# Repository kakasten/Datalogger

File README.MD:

# 🎲 Distributed Data Acquisition Platform for Race Vehicles

> A modular, scalable, engineering-driven architecture for high-performance vehicle instrumentation.

---

## 📖 Overview

This project is the development of a **distributed data acquisition platform** for race vehicles, designed to provide a modular, scalable, and easy-to-maintain architecture — capable of evolving continuously alongside the team's needs.

Built for **Formula SAE** vehicles, the system acquires data from analog, digital, frequency, and CAN sensors, transmits the information over a **CAN** network, and centralizes logging, processing, and telemetry in the Master module.

Unlike traditional systems, which centralize all instrumentation in a single acquisition unit, this platform adopts an architecture composed of one **Master module** and **multiple Slave modules**, distributed throughout the vehicle and placed close to the sensors they monitor.

**Key features:**

- ✅ Distributed acquisition
- ✅ CAN Bus communication
- ✅ Modular hardware
- ✅ Local data logging
- ✅ Telemetry support
- ✅ Fault isolation
- ✅ Expandable architecture

> More than a conventional datalogger, this is an open hardware, firmware, and documentation ecosystem, built to grow alongside the team.

---

## 🎯 The Problem We Solve

Centralized acquisition systems have well-known limitations in race vehicles:

- **Long, complex wiring harnesses**, with dozens of meters of cable running across the vehicle to a single central unit
- **High susceptibility to electromagnetic noise**, since low-amplitude analog signals must travel long distances before being conditioned
- **Difficult maintenance and expansion**, since every new sensor requires running a new cable to the central unit
- **Low scalability**, since expansion capacity is limited by the number of physical inputs on the central unit

Our approach solves these problems by **bringing processing to the sensor**, rather than the other way around.

---

## 🧩 System Architecture

### Selected Processing Units

The current hardware definition uses the following processing units:

| System role | Component | Responsibility |
| --- | --- | --- |
| Master | **Milk-V DUO S** (MPU) | High-level processing, data logging, telemetry, and system management |
| Slave | **STM32G431C8T6TR** (MCU) | Local sensor acquisition, signal processing, and CAN communication |

The platform is organized into two core functional blocks:

### 🔹 Master Module

The Master module is the platform's **central management point**. Its responsibilities include:

- Coordinating communication between the modules distributed across the vehicle
- Synchronizing data acquisition across all Slave modules
- Storing the data logged during vehicle operation
- Making data available to external analysis and development tools

The Master's architecture is designed to be **independent of specific implementation technologies** — allowing different software solutions, operating systems, communication protocols, or storage formats to be adopted as the project evolves, without compromising the platform's overall organization.

In the current implementation, the Master runs on the **Milk-V DUO S**, the selected **MPU (Microprocessor Unit)**, using an **RTOS (Real-Time Operating System)** as its software framework, responsible for coordinating logging, processing, and telemetry tasks.

### 🔹 Slave Modules

Slave modules are responsible for **local acquisition** of signals coming from the sensors. Close to the signal source, each module performs:

- Signal conditioning and filtering
- Analog-to-digital conversion
- Initial data processing
- Delivery of processed data to the vehicle's communication network

Each Slave is built around the **STM32G431C8T6TR**, the selected **MCU (Microcontroller Unit)**, responsible for local acquisition and for communicating over the **CAN** bus, which connects all modules to the Master.

Each module can be **specialized** according to the type of signal it needs to acquire:

| Module Type | Application |
| --- | --- |
| High-precision analog inputs | Pressure, temperature, potentiometer sensors |
| Digital inputs | On/off signals, buttons, limit switches |
| Timer capture | Wheel speed, RPM |
| Inertial sensors (IMU) | Acceleration, gyroscope |
| Suspension position | Vertical travel, suspension stroke |
| Custom modules | Application-specific sensors |

This specialization allows **hardware to be optimized for each module's function**, reducing cost, simplifying the electronic design, and increasing overall system reliability.

### 🔄 Communication Topology (High-Level View)

```text
                              ┌────────────────────────────┐
                              │           Master           │
                              │            MPU             │
                              │     RTOS • Data Logging    │
                              └────────────┬───────────────┘
                                           │
                                       CAN Network
                                           │
                 ┌─────────────────────────┴───────────────────────┐
                 │                                                 │
      ┌──────────▼──────────┐                           ┌──────────▼──────────┐
      │       Slave A       │                           │       Slave B       │
      │         MCU         │                           │         MCU         │
      │ Analog • Digital IO │                           │ Analog • Digital IO │
      └──────────┬──────────┘                           └──────────┬──────────┘
                 │                                                 │
          Vehicle Sensors                                   Vehicle Sensors
```

### 📊 Data Flow

1. Sensors generate raw electrical signals
2. Slave modules acquire and condition these signals locally
3. Measurements are transmitted over the **CAN** bus
4. The Master receives all messages from the network
5. Data is logged and, optionally, transmitted via real-time telemetry

### 🔗 Communication Architecture

Each communication interface is chosen based on bandwidth, latency, reliability, and hardware requirements:

- **CAN Bus** — the system's backbone, connecting the Master to one or more Slave modules
- **I²C / SPI / UART** — local interfaces between each module (Master or Slave) and its directly connected peripherals/sensors

```text
                              ┌─────────────────────────┐
                              │         Master          │
                              │           MPU           │
                              └────────────┬────────────┘
                                           │
                                      CAN Network
                                           │
                 ┌─────────────────────────┴───────────────────────┐
                 │                                                 │
      ┌──────────▼──────────┐                           ┌──────────▼──────────┐
      │       Slave A       │                           │       Slave B       │
      │         MCU         │                           │         MCU         │
      └──────────┬──────────┘                           └──────────┬──────────┘
                 │                                                 │
          I²C • SPI • UART                                  I²C • SPI • UART
                 │                                                 │
          Vehicle Sensors                                   Vehicle Sensors
```

---

## 🔌 Wiring Example

One of the main gains of the distributed architecture is the **drastic reduction in wiring harness complexity**. Instead of long individual cables running from each sensor to a central unit, each Slave module sits close to its own set of sensors, and only a shared communication bus runs across the vehicle.

**Conceptual comparison:**

| Aspect | Centralized System | Distributed System (this project) |
| --- | --- | --- |
| Total cable length | High | Reduced |
| Noise susceptibility | High (long analog signal runs) | Low (signal digitized close to source) |
| Ease of maintenance | Low | High |
| Scalability | Limited | High (just add a new module to the bus) |

---

## ⚙️ Engineering Philosophy

Since its inception, the project has prioritized a **clear separation between hardware, firmware, and development infrastructure**. Each component is developed as an independent module with well-defined interfaces, which ensures:

- ♻️ **Code reuse** across different modules and projects
- 🔧 **Simplified maintenance**, since each part can be modified independently
- 📈 **Easier future expansion**, without needing to restructure the entire platform
- 🔀 **Coexistence of hardware versions**, allowing gradual evolution without breaking compatibility

### 📚 Documented Engineering

More than a source code repository, this project is meant to be a **complete record of the engineering behind its development**. From the earliest stages, we aim to document:

- Architecture decisions and their technical rationale
- Functional diagrams and schematics
- Communication flows between modules
- Hardware version history
- Validation procedures and experimental results

This approach turns the repository into a **technical knowledge base**, valuable both for current developers and for future generations of the team.

---

## 🚀 Why Support This Project

This project goes beyond a one-off telemetry system — it represents an **investment in reusable engineering infrastructure**:

- **Common foundation for multiple applications**: rather than a one-off solution, the platform serves as a foundation for different instrumentation systems, from low-frequency measurements to high-speed signals requiring precise timing
- **Technical development for the team**: development spans embedded hardware, firmware, communication protocols, software engineering, and technical documentation — high-value skills for team members
- **Visibility and branding**: the project's public, well-structured documentation serves as a technical showcase for sponsors and partners
- **Continuity**: the emphasis on documentation and modularity ensures that today's investment keeps generating value across future generations of the system

Companies and sponsors interested in supporting the project can get in touch through the channels listed in the [Contact](#-contact) section.

---

## 🤝 Contributing

Contributions are welcome! To propose improvements, fixes, or new features:

1. Fork this repository
2. Create a branch for your change (`git checkout -b feature/feature-name`)
3. Commit your changes (`git commit -m 'Add new feature'`)
4. Push to the remote repository (`git push origin feature/feature-name`)
5. Open a Pull Request

---

## 📬 Contact

For questions, partnerships, or sponsorship proposals, get in touch with the team:

- **Email:** _luizfernandosilveriofelisbino@gmail.com_

---

## 📄 License

This project is distributed under the **[Apache License 2.0](LICENSE)**.

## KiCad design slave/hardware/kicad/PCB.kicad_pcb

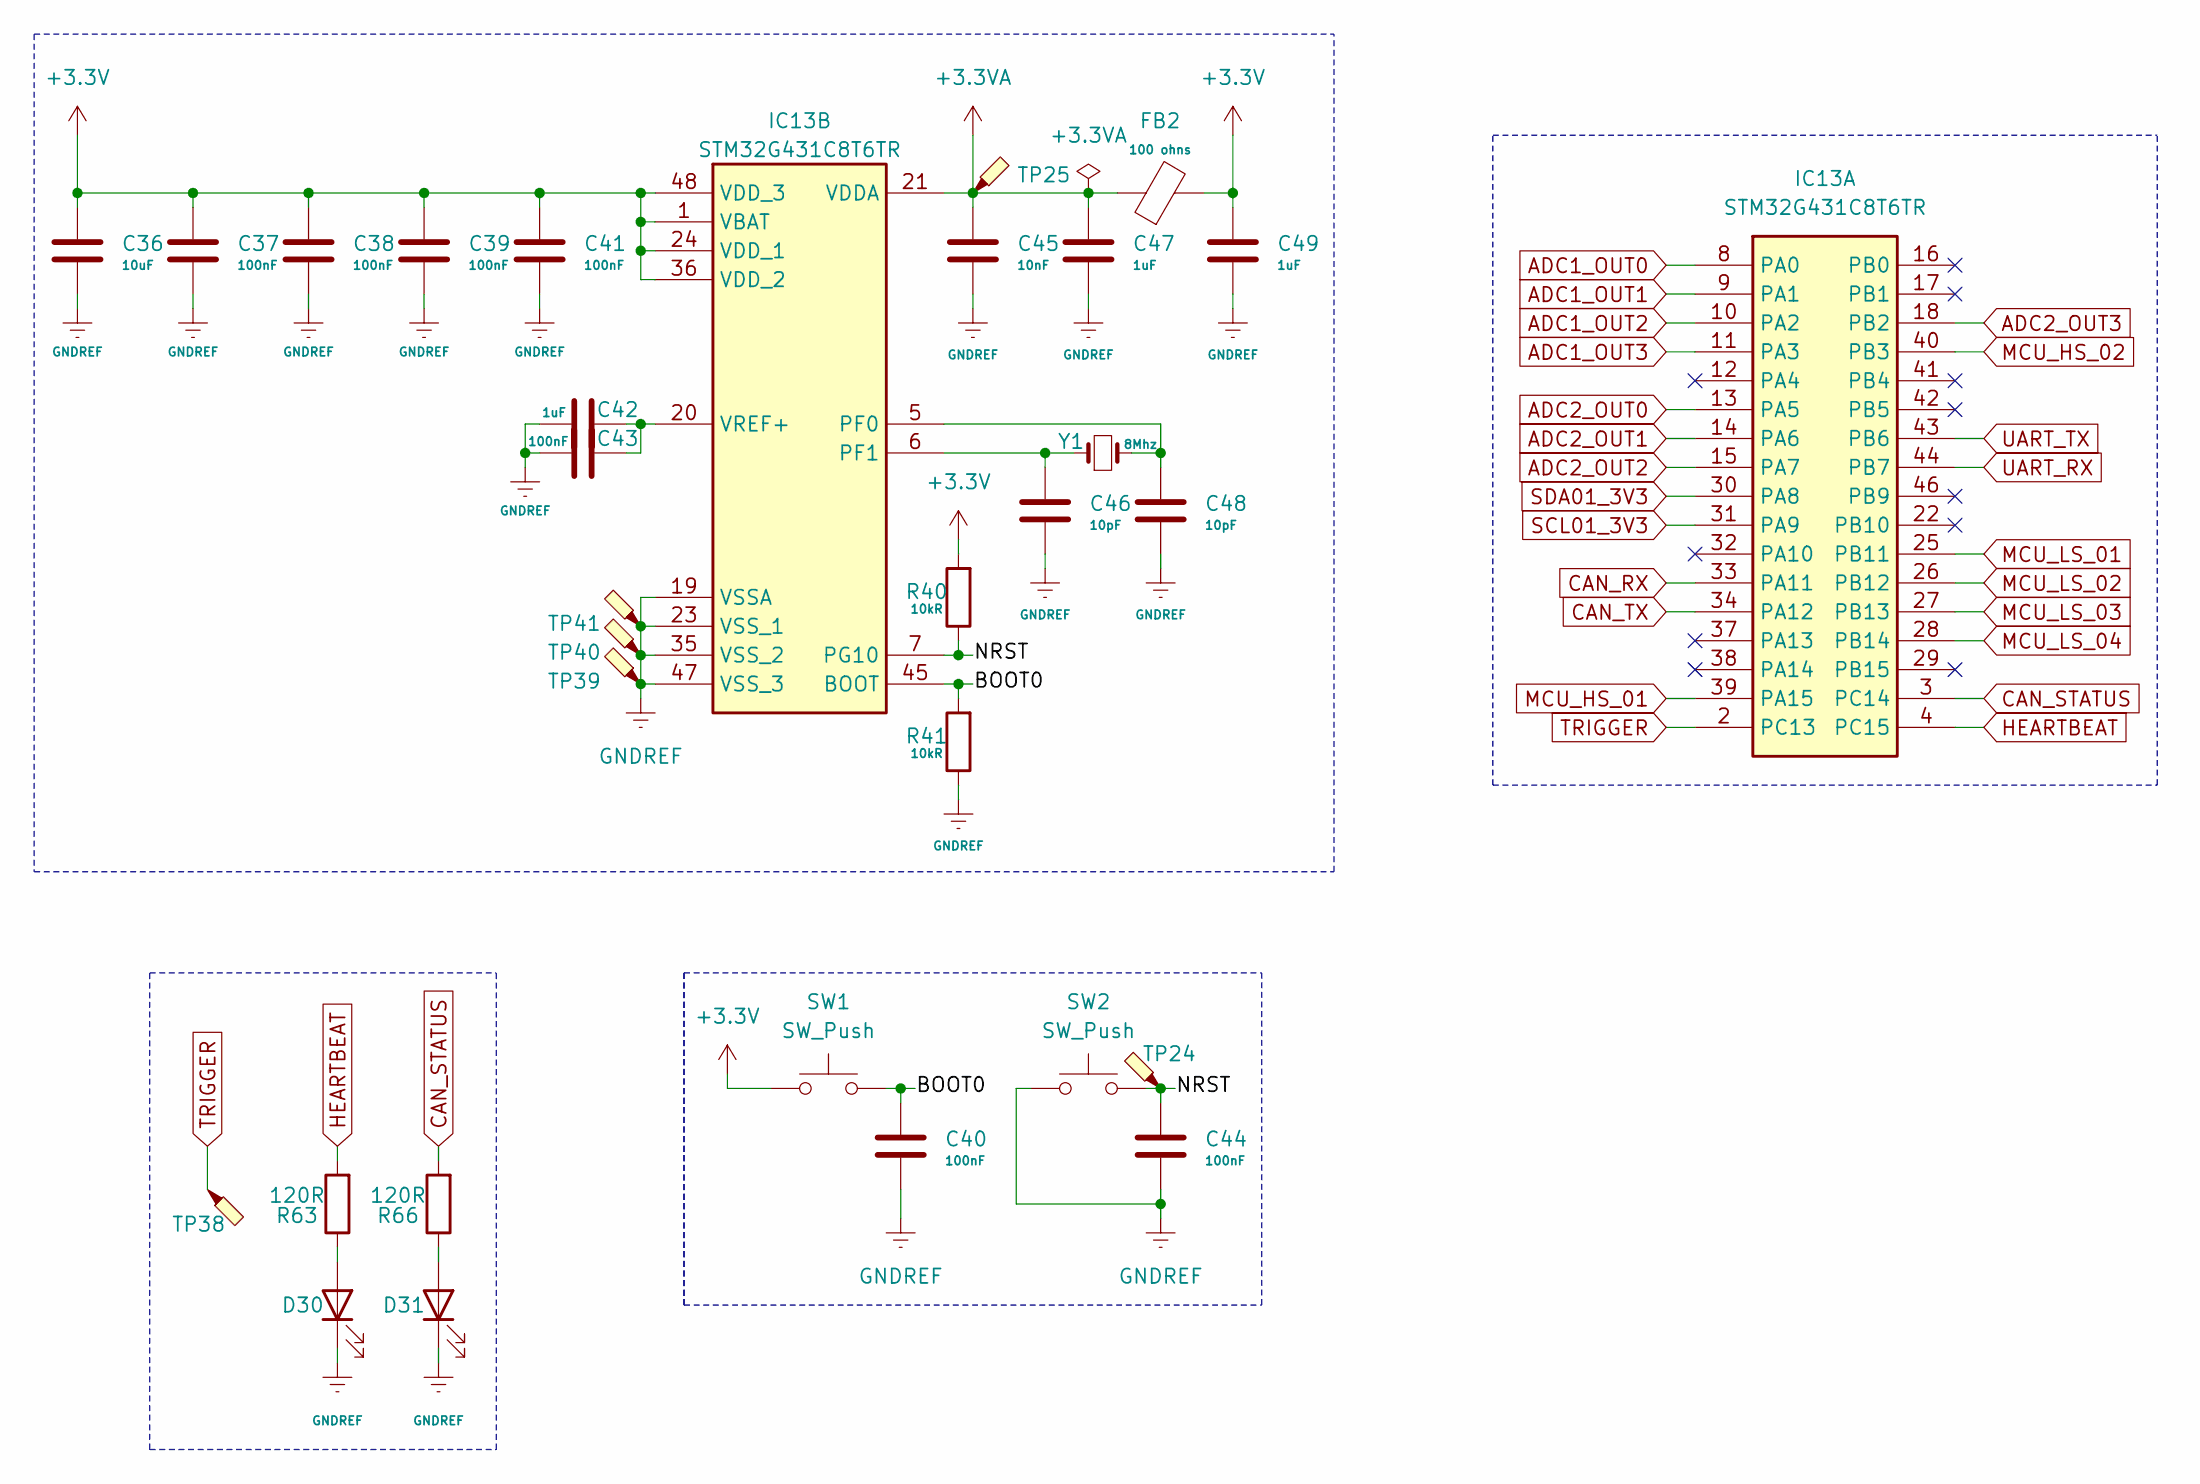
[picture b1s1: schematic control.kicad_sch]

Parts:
C36: 10uF; C_0603_1608Metric
C37, C38, C39, C40, C41, C43, C44: 100nF; C_0603_1608Metric
C42, C47, C49: 1uF; C_0603_1608Metric
C45: 10nF; C_0603_1608Metric
C46, C48: 10pF; C_0603_1608Metric
D30, D31: LED; LED_0805_2012Metric
FB2: 100 ohns; C_0603_1608Metric
IC13: STM32G431C8T6TR; QFP50P900X900X160-48N; Mouser Part Number 511-STM32G431C8T6TR
R40, R41: 10kR; R_0805_2012Metric
R63, R66: 120R; R_0805_2012Metric
SW1, SW2: SW_Push; SW_SPST_CK_RS282G05A3
TP24, TP25: TestPoint_Pad_2.0x2.0mm
TP38, TP39, TP40, TP41: TestPoint_Bridge_Pitch2.0mm_Drill0.7mm
Y1: 8Mhz; Crystal_SMD_WE_CFPX-180-4Pin_3.2x2.5mm

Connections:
+3.3V: C36.1, C37.1, C38.1, C39.1, C41.1, C49.1, FB2.2, IC13.1 (VBAT), IC13.24 (VDD_1), IC13.36 (VDD_2), IC13.48 (VDD_3), R40.2, SW1.1; also elsewhere on the board
+3.3VA: C45.1, C47.1, FB2.1, IC13.21 (VDDA), TP25.1 (1_1); also elsewhere on the board
/Control/BOOT0: C40.1, IC13.45 (BOOT), R41.2, SW1.2
/Control/NRST: C44.1, IC13.7 (PG10), R40.1, SW2.2, TP24.1 (1_1)
ADC1_OUT0: IC13.8 (PA0); also elsewhere on the board
ADC1_OUT1: IC13.9 (PA1); also elsewhere on the board
ADC1_OUT2: IC13.10 (PA2); also elsewhere on the board
ADC1_OUT3: IC13.11 (PA3); also elsewhere on the board
ADC2_OUT0: IC13.13 (PA5); also elsewhere on the board
ADC2_OUT1: IC13.14 (PA6); also elsewhere on the board
ADC2_OUT2: IC13.15 (PA7); also elsewhere on the board
ADC2_OUT3: IC13.18 (PB2); also elsewhere on the board
CAN_RX: IC13.33 (PA11); also elsewhere on the board
CAN_STATUS: IC13.3 (PC14), R66.2
CAN_TX: IC13.34 (PA12); also elsewhere on the board
GNDREF: C36.2, C37.2, C38.2, C39.2, C40.2, C41.2, C42.1, C43.1, C44.2, C45.2, C46.2, C47.2, C48.2, C49.2, D30.1 (K), D31.1 (K), IC13.19 (VSSA), IC13.23 (VSS_1), IC13.35 (VSS_2), IC13.47 (VSS_3), R41.1, SW2.1, TP39.1 (1_1), TP40.1 (1_1), TP41.1 (1_1); also elsewhere on the board
HEARTBEAT: IC13.4 (PC15), R63.2
MCU_HS_01: IC13.39 (PA15); also elsewhere on the board
MCU_HS_02: IC13.40 (PB3); also elsewhere on the board
MCU_LS_01: IC13.25 (PB11); also elsewhere on the board
MCU_LS_02: IC13.26 (PB12); also elsewhere on the board
MCU_LS_03: IC13.27 (PB13); also elsewhere on the board
MCU_LS_04: IC13.28 (PB14); also elsewhere on the board
unnamed: D30.2 (A), R63.1
unnamed: D31.2 (A), R66.1
unnamed: C48.1, IC13.5 (PF0), Y1.2
unnamed: C46.1, IC13.6 (PF1), Y1.1
unnamed: C42.2, C43.2, IC13.20 (VREF+)
SCL01_3V3: IC13.31 (PA9); also elsewhere on the board
SDA01_3V3: IC13.30 (PA8); also elsewhere on the board
TRIGGER: IC13.2 (PC13), TP38.1 (1_1)
UART_RX: IC13.44 (PB7); also elsewhere on the board
UART_TX: IC13.43 (PB6); also elsewhere on the board

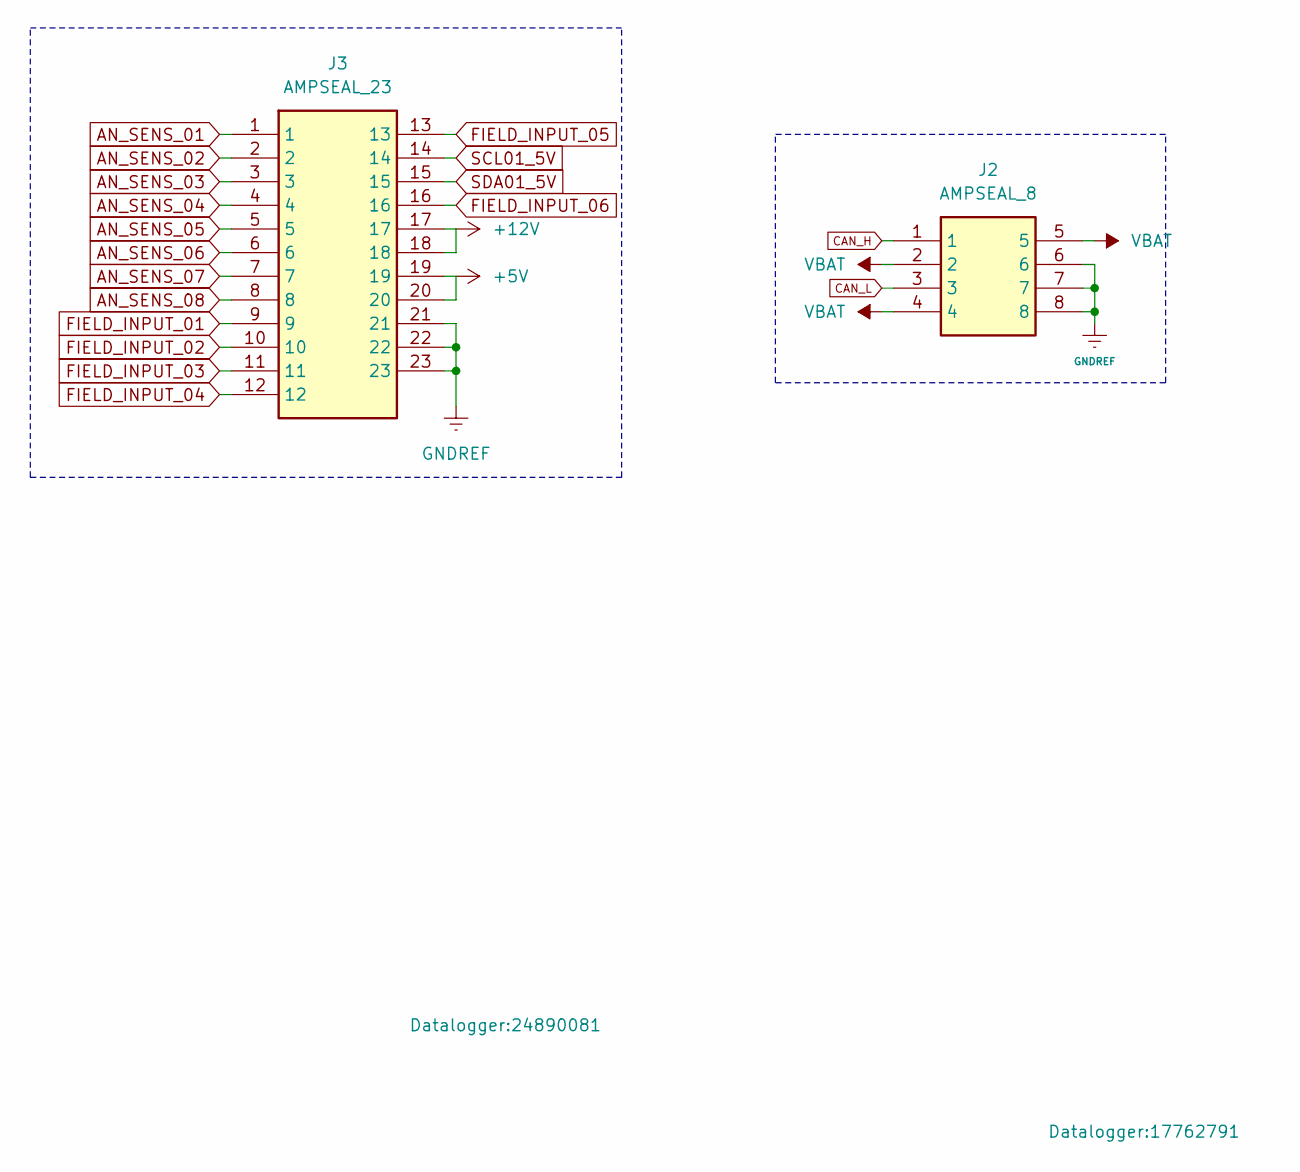
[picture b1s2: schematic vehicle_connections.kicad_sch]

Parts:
J2: AMPSEAL_8; 17762791; Mouser Part Number 571-1-776279-1
J3: AMPSEAL_23; 24890081; Manufacturer_Part_Number 2489008-1

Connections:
+5V: J3.19, J3.20; also elsewhere on the board
+12V: J3.17, J3.18; also elsewhere on the board
AN_SENS_01: J3.1; also elsewhere on the board
AN_SENS_02: J3.2; also elsewhere on the board
AN_SENS_03: J3.3; also elsewhere on the board
AN_SENS_04: J3.4; also elsewhere on the board
AN_SENS_05: J3.5; also elsewhere on the board
AN_SENS_06: J3.6; also elsewhere on the board
AN_SENS_07: J3.7; also elsewhere on the board
AN_SENS_08: J3.8; also elsewhere on the board
CAN_H: J2.1; also elsewhere on the board
CAN_L: J2.3; also elsewhere on the board
FIELD_INPUT_01: J3.9; also elsewhere on the board
FIELD_INPUT_02: J3.10; also elsewhere on the board
FIELD_INPUT_03: J3.11; also elsewhere on the board
FIELD_INPUT_04: J3.12; also elsewhere on the board
FIELD_INPUT_05: J3.13; also elsewhere on the board
FIELD_INPUT_06: J3.16; also elsewhere on the board
GNDREF: J2.6, J2.7, J2.8, J3.21, J3.22, J3.23; also elsewhere on the board
SCL01_5V: J3.14; also elsewhere on the board
SDA01_5V: J3.15; also elsewhere on the board
VBAT: J2.2, J2.4, J2.5; also elsewhere on the board

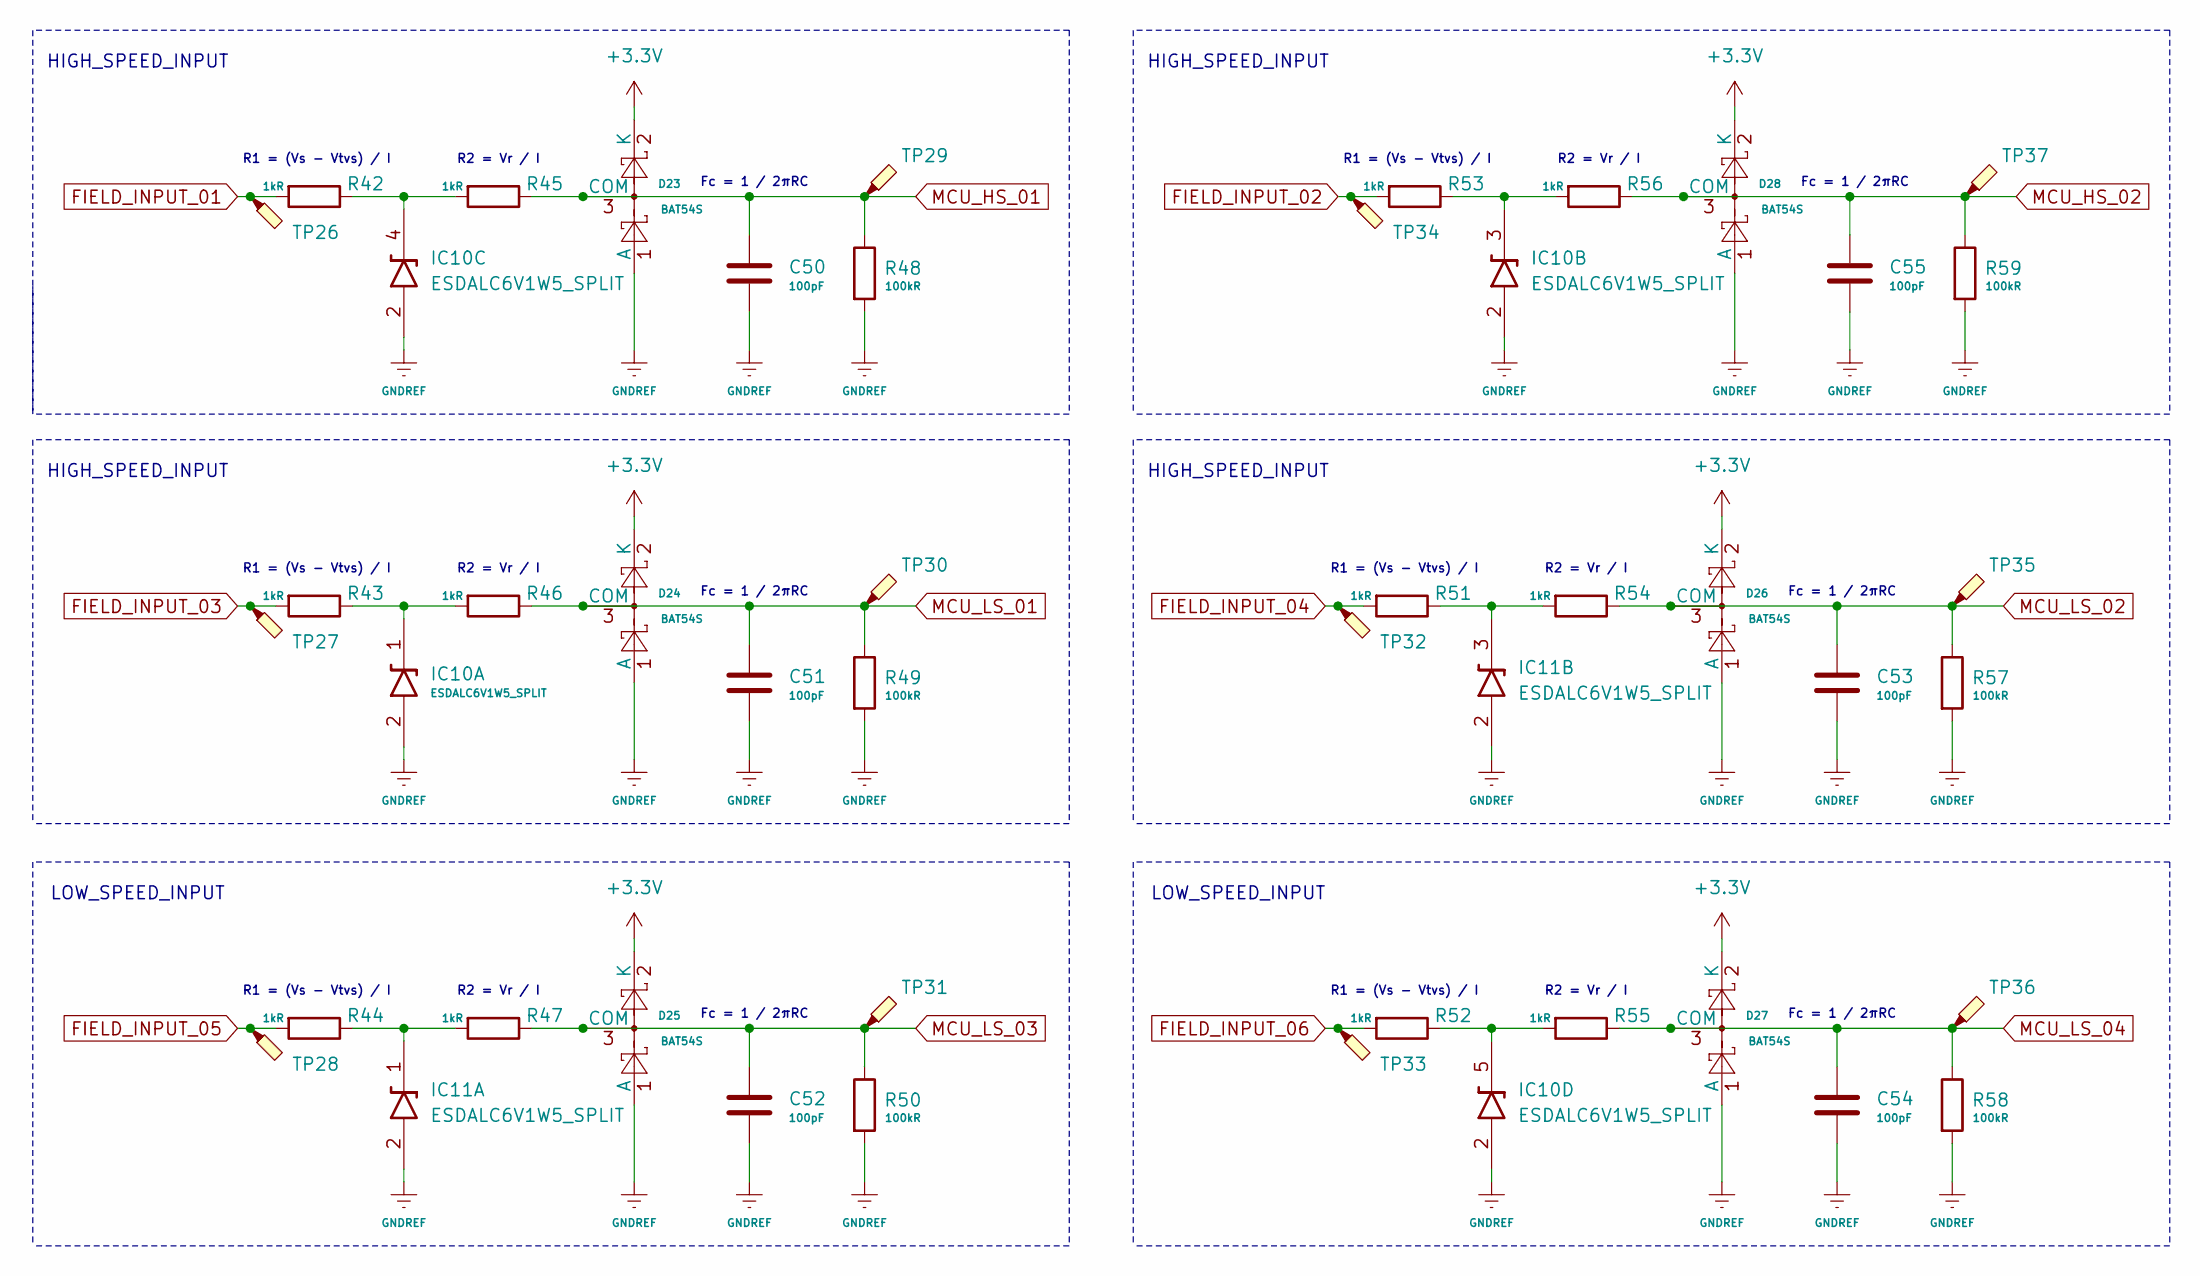
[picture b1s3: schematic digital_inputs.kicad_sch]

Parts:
C50, C51, C52, C53, C54, C55: 100pF; C_0603_1608Metric
D23, D24, D25, D26, D27, D28: BAT54S; SOT-23
IC10, IC11: ESDALC6V1W5_SPLIT; SOT65P210X110-5N; Mouser Part Number 511-ESDALC6V1W5
R42, R43, R44, R45, R46, R47, R51, R52, R53, R54, R55, R56: 1kR; R_1210_3225Metric
R48, R49, R50, R57, R58, R59: 100kR; R_0805_2012Metric
TP26, TP27, TP28, TP29, TP30, TP31, TP32, TP33, TP34, TP35, TP36, TP37: TestPoint_Pad_2.0x2.0mm

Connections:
+3.3V: D23.2 (K), D24.2 (K), D25.2 (K), D26.2 (K), D27.2 (K), D28.2 (K); also elsewhere on the board
FIELD_INPUT_01: R42.2, TP26.1 (1_1); also elsewhere on the board
FIELD_INPUT_02: R53.2, TP34.1 (1_1); also elsewhere on the board
FIELD_INPUT_03: R43.2, TP27.1 (1_1); also elsewhere on the board
FIELD_INPUT_04: R51.2, TP32.1 (1_1); also elsewhere on the board
FIELD_INPUT_05: R44.2, TP28.1 (1_1); also elsewhere on the board
FIELD_INPUT_06: R52.2, TP33.1 (1_1); also elsewhere on the board
GNDREF: C50.2, C51.2, C52.2, C53.2, C54.2, C55.2, D23.1 (A), D24.1 (A), D25.1 (A), D26.1 (A), D27.1 (A), D28.1 (A), IC10.2, IC11.2, R48.2, R49.2, R50.2, R57.2, R58.2, R59.2; also elsewhere on the board
MCU_HS_01: C50.1, D23.3 (COM), R45.1, R48.1, TP29.1 (1_1); also elsewhere on the board
MCU_HS_02: C55.1, D28.3 (COM), R56.1, R59.1, TP37.1 (1_1); also elsewhere on the board
MCU_LS_01: C51.1, D24.3 (COM), R46.1, R49.1, TP30.1 (1_1); also elsewhere on the board
MCU_LS_02: C53.1, D26.3 (COM), R54.1, R57.1, TP35.1 (1_1); also elsewhere on the board
MCU_LS_03: C52.1, D25.3 (COM), R47.1, R50.1, TP31.1 (1_1); also elsewhere on the board
MCU_LS_04: C54.1, D27.3 (COM), R55.1, R58.1, TP36.1 (1_1); also elsewhere on the board
unnamed: IC10.1, R43.1, R46.2
unnamed: IC10.3, R53.1, R56.2
unnamed: IC10.4, R42.1, R45.2
unnamed: IC10.5, R52.1, R55.2
unnamed: IC11.1, R44.1, R47.2
unnamed: IC11.3, R51.1, R54.2

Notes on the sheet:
HIGH_SPEED_INPUT
R2 = Vr / I
LOW_SPEED_INPUT
Fc = 1 / 2πRC
R1 = (Vs - Vtvs) / I

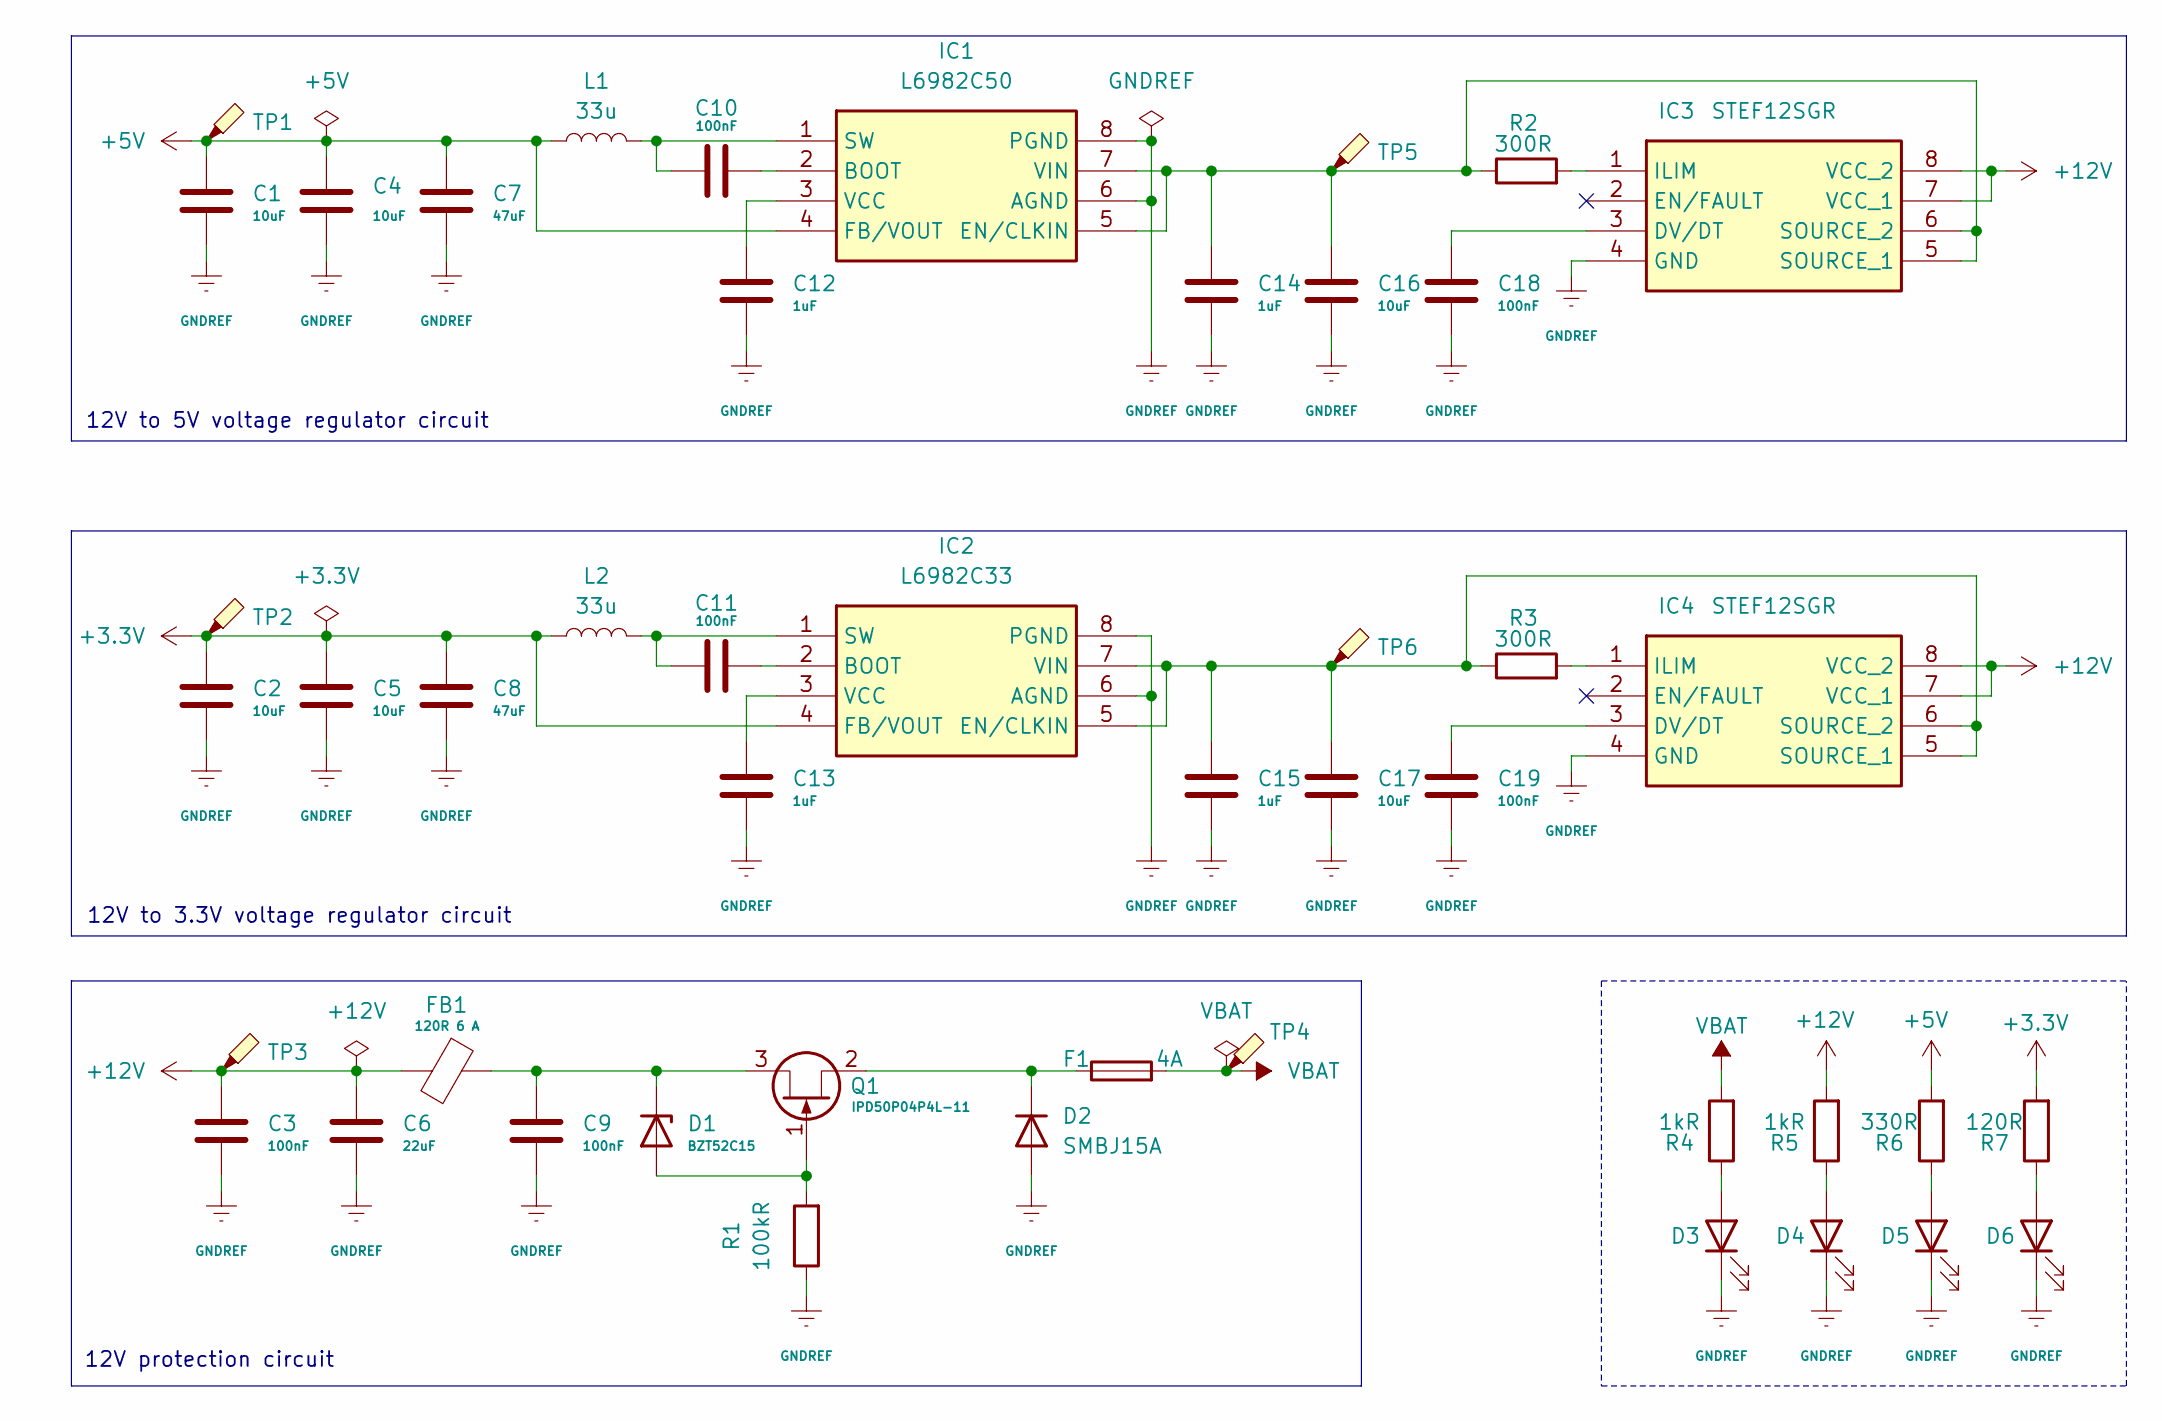
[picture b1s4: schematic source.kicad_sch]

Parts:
C1, C2, C4, C5, C16, C17: 10uF; C_0603_1608Metric
C3, C9, C10, C11, C18, C19: 100nF; C_0603_1608Metric
C6: 22uF; C_0603_1608Metric
C7, C8: 47uF; C_0603_1608Metric
C12, C13, C14, C15: 1uF; C_0603_1608Metric
D1: BZT52C15; D_SOD-123
D2: SMBJ15A; D_SMB
D3, D4, D5, D6: LED; LED_0805_2012Metric
F1: 4A; Fuse_0805_2012Metric
FB1: 120R 6 A; L_1206_3216Metric
IC1: L6982C50; SOIC127P600X175-8N; Mouser Part Number 511-L6982CDR
IC2: L6982C33; SOIC127P600X175-8N; Mouser Part Number 511-L6982CDR
IC3, IC4: STEF12SGR; SOP65P280X100-8N; Mouser Part Number 511-STEF12SGR
L1, L2: 33u; L_Coilcraft_MSS1246T-XXX
Q1: IPD50P04P4L-11; TO-252-2
R1: 100kR; R_0805_2012Metric
R2, R3: 300R; R_0805_2012Metric
R4, R5: 1kR; R_0805_2012Metric
R6: 330R; R_0805_2012Metric
R7: 120R; R_0805_2012Metric
TP1, TP2, TP3, TP4, TP5, TP6: TestPoint_Pad_2.0x2.0mm

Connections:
+3.3V: C2.1, C5.1, C8.1, IC2.4 (FB/VOUT), L2.1, R7.2, TP2.1 (1_1); also elsewhere on the board
+5V: C1.1, C4.1, C7.1, IC1.4 (FB/VOUT), L1.1, R6.2, TP1.1 (1_1); also elsewhere on the board
+12V: C3.1, C6.1, FB1.2, IC3.7 (VCC_1), IC3.8 (VCC_2), IC4.7 (VCC_1), IC4.8 (VCC_2), R5.2, TP3.1 (1_1); also elsewhere on the board
GNDREF: C1.2, C2.2, C3.2, C4.2, C5.2, C6.2, C7.2, C8.2, C9.2, C12.2, C13.2, C14.2, C15.2, C16.2, C17.2, C18.2, C19.2, D2.2 (A), D3.1 (K), D4.1 (K), D5.1 (K), D6.1 (K), IC1.6 (AGND), IC1.8 (PGND), IC2.6 (AGND), IC2.8 (PGND), IC3.4 (GND), IC4.4 (GND), R1.1; also elsewhere on the board
unnamed: D1.2 (A), Q1.1 (G), R1.2
unnamed: C9.1, D1.1 (K), FB1.1, Q1.3 (D)
unnamed: D2.1 (K), F1.1, Q1.2 (S)
unnamed: D3.2 (A), R4.1
unnamed: D4.2 (A), R5.1
unnamed: D5.2 (A), R6.1
unnamed: D6.2 (A), R7.1
unnamed: C10.1, IC1.2 (BOOT)
unnamed: C14.1, C16.1, IC1.5 (EN/CLKIN), IC1.7 (VIN), IC3.5 (SOURCE_1), IC3.6 (SOURCE_2), R2.1, TP5.1 (1_1)
unnamed: C10.2, IC1.1 (SW), L1.2
unnamed: C12.1, IC1.3 (VCC)
unnamed: C11.1, IC2.2 (BOOT)
unnamed: C15.1, C17.1, IC2.5 (EN/CLKIN), IC2.7 (VIN), IC4.5 (SOURCE_1), IC4.6 (SOURCE_2), R3.1, TP6.1 (1_1)
unnamed: C11.2, IC2.1 (SW), L2.2
unnamed: C13.1, IC2.3 (VCC)
unnamed: C18.1, IC3.3 (DV/DT)
unnamed: IC3.1 (ILIM), R2.2
unnamed: C19.1, IC4.3 (DV/DT)
unnamed: IC4.1 (ILIM), R3.2
VBAT: F1.2, R4.2, TP4.1 (1_1); also elsewhere on the board

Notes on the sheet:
12V protection circuit
12V to 5V voltage regulator circuit
12V to 3.3V voltage regulator circuit

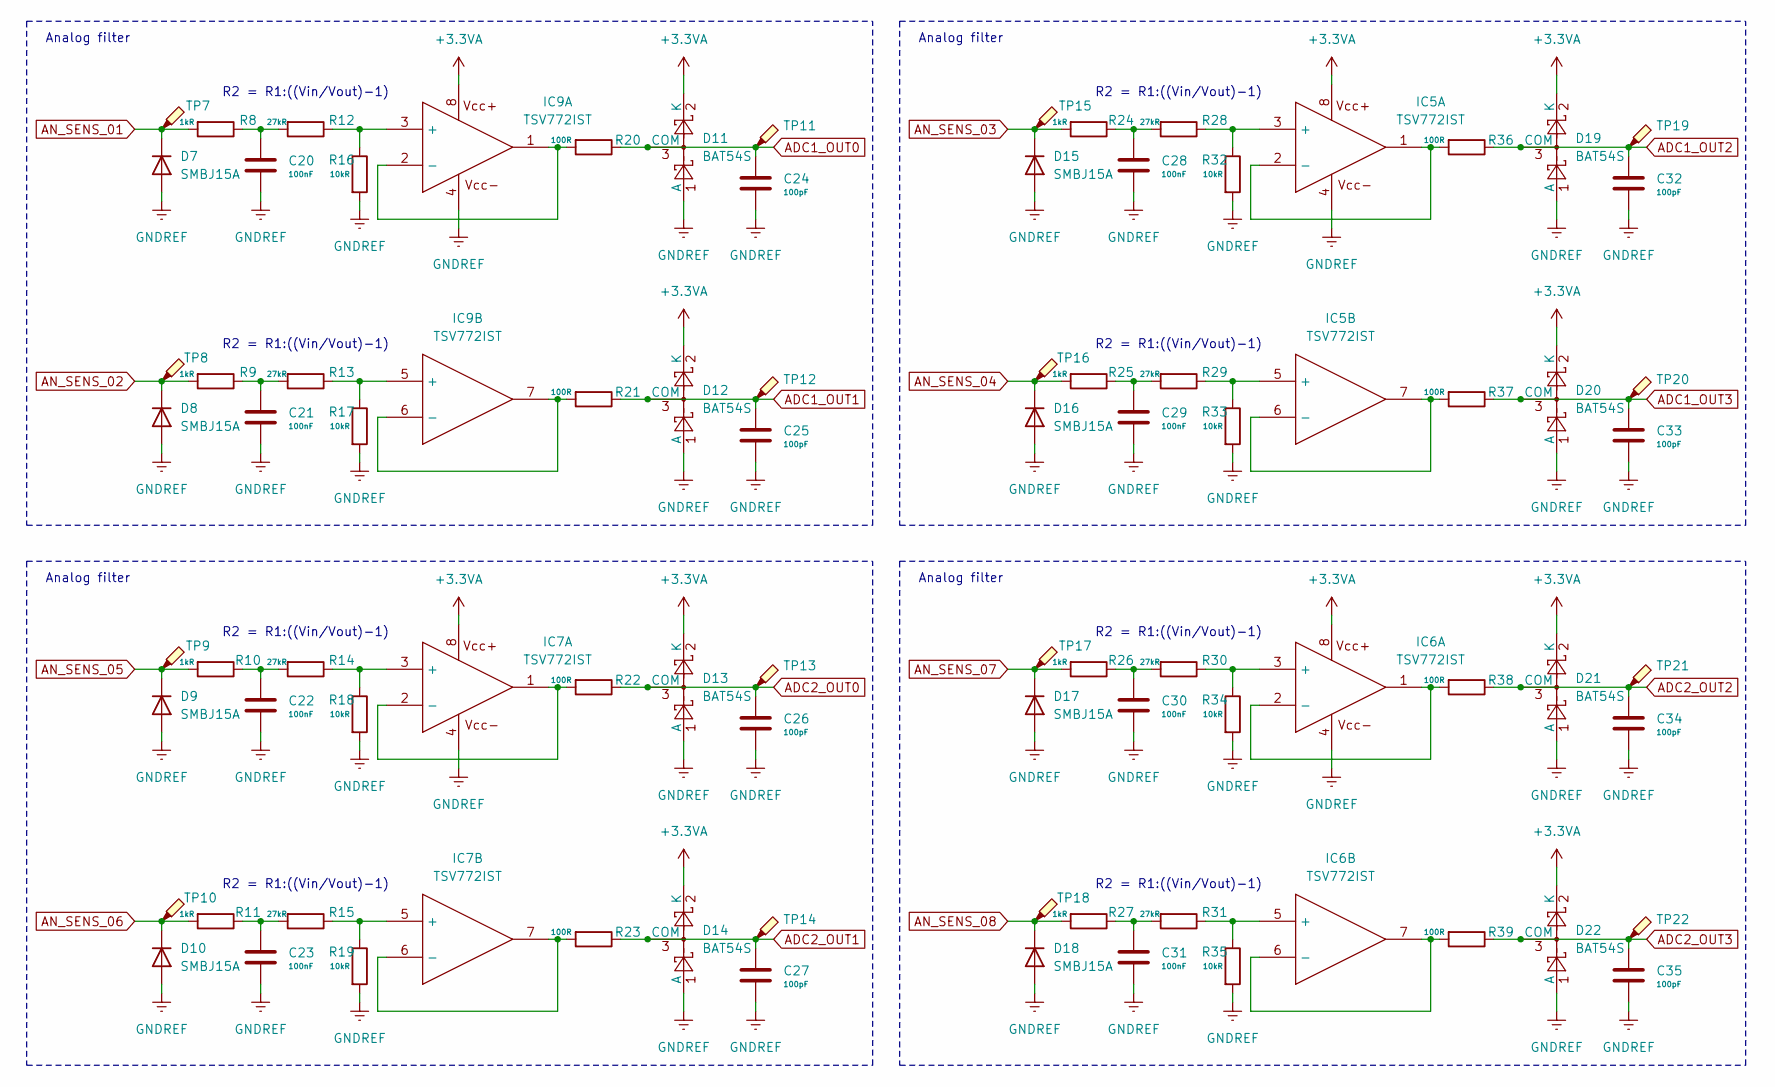
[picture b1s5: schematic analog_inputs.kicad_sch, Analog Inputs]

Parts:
C20, C21, C22, C23, C28, C29, C30, C31: 100nF; C_0603_1608Metric
C24, C25, C26, C27, C32, C33, C34, C35: 100pF; C_0603_1608Metric
D7, D8, D9, D10, D15, D16, D17, D18: SMBJ15A; D_SMB
D11, D12, D13, D14, D19, D20, D21, D22: BAT54S; SOT-23
IC5, IC6, IC7, IC9: TSV772IST; SOP65P490X110-8N; Mouser Part Number 511-TSV772IST
R8, R9, R10, R11, R24, R25, R26, R27: 1kR; R_0805_2012Metric
R12, R13, R14, R15, R28, R29, R30, R31: 27kR; R_0805_2012Metric
R16, R17, R18, R19, R32, R33, R34, R35: 10kR; R_0805_2012Metric
R20, R21, R22, R23, R36, R37, R38, R39: 100R; R_0805_2012Metric
TP7, TP8, TP9, TP10, TP11, TP12, TP13, TP14, TP15, TP16, TP17, TP18, TP19, TP20, TP21, TP22: TestPoint_Pad_2.0x2.0mm

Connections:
+3.3VA: D11.2 (K), D12.2 (K), D13.2 (K), D14.2 (K), D19.2 (K), D20.2 (K), D21.2 (K), D22.2 (K), IC5.8, IC6.8, IC7.8, IC9.8; also elsewhere on the board
ADC1_OUT0: C24.1, D11.3 (COM), R20.1, TP11.1 (1_1); also elsewhere on the board
ADC1_OUT1: C25.1, D12.3 (COM), R21.1, TP12.1 (1_1); also elsewhere on the board
ADC1_OUT2: C32.1, D19.3 (COM), R36.1, TP19.1 (1_1); also elsewhere on the board
ADC1_OUT3: C33.1, D20.3 (COM), R37.1, TP20.1 (1_1); also elsewhere on the board
ADC2_OUT0: C26.1, D13.3 (COM), R22.1, TP13.1 (1_1); also elsewhere on the board
ADC2_OUT1: C27.1, D14.3 (COM), R23.1, TP14.1 (1_1); also elsewhere on the board
ADC2_OUT2: C34.1, D21.3 (COM), R38.1, TP21.1 (1_1); also elsewhere on the board
ADC2_OUT3: C35.1, D22.3 (COM), R39.1, TP22.1 (1_1); also elsewhere on the board
AN_SENS_01: D7.1 (K), R8.2, TP7.1 (1_1); also elsewhere on the board
AN_SENS_02: D8.1 (K), R9.2, TP8.1 (1_1); also elsewhere on the board
AN_SENS_03: D15.1 (K), R24.2, TP15.1 (1_1); also elsewhere on the board
AN_SENS_04: D16.1 (K), R25.2, TP16.1 (1_1); also elsewhere on the board
AN_SENS_05: D9.1 (K), R10.2, TP9.1 (1_1); also elsewhere on the board
AN_SENS_06: D10.1 (K), R11.2, TP10.1 (1_1); also elsewhere on the board
AN_SENS_07: D17.1 (K), R26.2, TP17.1 (1_1); also elsewhere on the board
AN_SENS_08: D18.1 (K), R27.2, TP18.1 (1_1); also elsewhere on the board
GNDREF: C20.2, C21.2, C22.2, C23.2, C24.2, C25.2, C26.2, C27.2, C28.2, C29.2, C30.2, C31.2, C32.2, C33.2, C34.2, C35.2, D7.2 (A), D8.2 (A), D9.2 (A), D10.2 (A), D11.1 (A), D12.1 (A), D13.1 (A), D14.1 (A), D15.2 (A), D16.2 (A), D17.2 (A), D18.2 (A), D19.1 (A), D20.1 (A), D21.1 (A), D22.1 (A), IC5.4, IC6.4, IC7.4, IC9.4, R16.2, R17.2, R18.2, R19.2, R32.2, R33.2, R34.2, R35.2; also elsewhere on the board
unnamed: C20.1, R8.1, R12.2
unnamed: C21.1, R9.1, R13.2
unnamed: C22.1, R10.1, R14.2
unnamed: C23.1, R11.1, R15.2
unnamed: C28.1, R24.1, R28.2
unnamed: C29.1, R25.1, R29.2
unnamed: C30.1, R26.1, R30.2
unnamed: C31.1, R27.1, R31.2
unnamed: IC5.3 (+), R28.1, R32.1
unnamed: IC5.1, IC5.2 (-), R36.2
unnamed: IC5.5 (+), R29.1, R33.1
unnamed: IC5.6 (-), IC5.7, R37.2
unnamed: IC6.3 (+), R30.1, R34.1
unnamed: IC6.1, IC6.2 (-), R38.2
unnamed: IC6.5 (+), R31.1, R35.1
unnamed: IC6.6 (-), IC6.7, R39.2
unnamed: IC7.3 (+), R14.1, R18.1
unnamed: IC7.1, IC7.2 (-), R22.2
unnamed: IC7.5 (+), R15.1, R19.1
unnamed: IC7.6 (-), IC7.7, R23.2
unnamed: IC9.3 (+), R12.1, R16.1
unnamed: IC9.1, IC9.2 (-), R20.2
unnamed: IC9.5 (+), R13.1, R17.1
unnamed: IC9.6 (-), IC9.7, R21.2

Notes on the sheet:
R2 = R1:((Vin/Vout)-1)
Analog filter

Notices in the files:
README.MD:
License: Apache 2.0
